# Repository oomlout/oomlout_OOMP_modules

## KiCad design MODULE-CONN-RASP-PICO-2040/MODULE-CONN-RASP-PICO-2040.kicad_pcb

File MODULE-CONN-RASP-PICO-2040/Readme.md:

Contents
========

* [MCRP2040 > ](#mcrp2040--)
	* [OOMP Parts](#oomp-parts)
	* [Images](#images)
	* [Tags](#tags)
  
![][im]
# MCRP2040 > 

- ID: MODULE-CONN-RASP-PICO-2040
- Hex ID: MCRP2040
- Name: 
- Description: 
- Long Link: [http://oom.lt/MODULE-CONN-RASP-PICO-2040](http://oom.lt/MODULE-CONN-RASP-PICO-2040)
- Short Link: [http://oom.lt/MCRP2040](http://oom.lt/MCRP2040)

## OOMP Parts

|OOMP ID|Name|Identifier|
| :---: | :---: | :---: |
|[HEAD-I01-X-PI20-01](https://github.com/oomlout/oomlout_OOMP_parts/tree/main/HEAD-I01-X-PI20-01/)|[2.54 mm 20 Pin Header](https://github.com/oomlout/oomlout_OOMP_parts/tree/main/HEAD-I01-X-PI20-01/)|[J1, J2](https://github.com/oomlout/oomlout_OOMP_parts/tree/main/HEAD-I01-X-PI20-01/)|

## Images

|kicadPcb3d|kicadPcb3dFront|kicadPcb3dBack|kicadSchem|pcbdraw|pcbdrawback|
| :---: | :---: | :---: | :---: | :---: | :---: |
|||||||

## Tags

- oompType: MODULE
- oompSize: CONN
- oompColor: RASP
- oompDesc: PICO
- oompIndex: 2040
- matchingBlock: BLOCK-CONN-RASP-PICO-2040
- oompParts: J1,HEAD-I01-X-PI20-01
- oompParts: J2,HEAD-I01-X-PI20-01
- hexID: MCRP2040
- oompID: MODULE-CONN-RASP-PICO-2040

[im]: kicadPcb3d_450.png

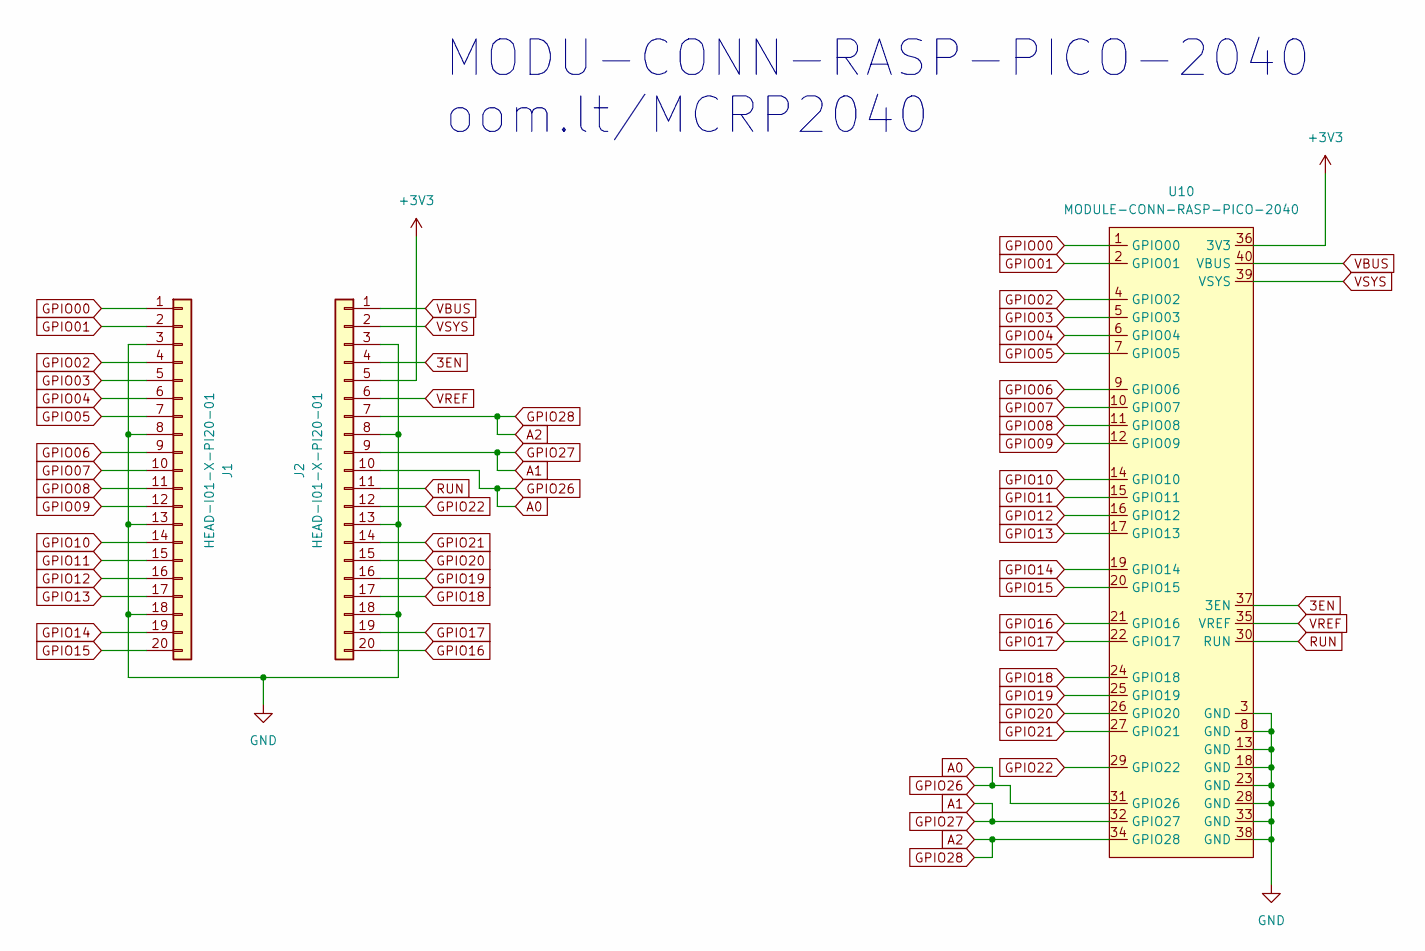
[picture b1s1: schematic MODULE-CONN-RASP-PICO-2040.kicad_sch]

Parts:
J1, J2: HEAD-I01-X-PI20-01; PinHeader_1x20_P2.54mm_Vertical
U10: MODULE-CONN-RASP-PICO-2040

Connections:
3EN: J2.4, U10.37 (3EN)
+3V3: J2.5, U10.36 (3V3)
GND: J1.3, J1.8, J1.13, J1.18, J2.3, J2.8, J2.13, J2.18, U10.3 (GND), U10.8 (GND), U10.13 (GND), U10.18 (GND), U10.23 (GND), U10.28 (GND), U10.33 (GND), U10.38 (GND)
GPIO00: J1.1, U10.1 (GPIO00)
GPIO01: J1.2, U10.2 (GPIO01)
GPIO02: J1.4, U10.4 (GPIO02)
GPIO03: J1.5, U10.5 (GPIO03)
GPIO04: J1.6, U10.6 (GPIO04)
GPIO05: J1.7, U10.7 (GPIO05)
GPIO06: J1.9, U10.9 (GPIO06)
GPIO07: J1.10, U10.10 (GPIO07)
GPIO08: J1.11, U10.11 (GPIO08)
GPIO09: J1.12, U10.12 (GPIO09)
GPIO10: J1.14, U10.14 (GPIO10)
GPIO11: J1.15, U10.15 (GPIO11)
GPIO12: J1.16, U10.16 (GPIO12)
GPIO13: J1.17, U10.17 (GPIO13)
GPIO14: J1.19, U10.19 (GPIO14)
GPIO15: J1.20, U10.20 (GPIO15)
GPIO16: J2.20, U10.21 (GPIO16)
GPIO17: J2.19, U10.22 (GPIO17)
GPIO18: J2.17, U10.24 (GPIO18)
GPIO19: J2.16, U10.25 (GPIO19)
GPIO20: J2.15, U10.26 (GPIO20)
GPIO21: J2.14, U10.27 (GPIO21)
GPIO22: J2.12, U10.29 (GPIO22)
GPIO26: J2.10, U10.31 (GPIO26)
GPIO27: J2.9, U10.32 (GPIO27)
GPIO28: J2.7, U10.34 (GPIO28)
RUN: J2.11, U10.30 (RUN)
VBUS: J2.1, U10.40 (VBUS)
VREF: J2.6, U10.35 (VREF)
VSYS: J2.2, U10.39 (VSYS)

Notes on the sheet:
MODU-CONN-RASP-PICO-2040 oom.lt/MCRP2040

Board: 2 copper layers, 4 parts (0 on the bottom side), 33 nets, no tracks yet.

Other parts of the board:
Ref**: Val**; silkscreen

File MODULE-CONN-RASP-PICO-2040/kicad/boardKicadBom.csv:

"Id";"Designator";"Package";"Quantity";"Designation";"Supplier and ref";
1;"U10";"MODULE-CONN-RASP-PICO-2040";1;"MODULE-CONN-RASP-PICO-2040";;;
2;"J1,J2";"PinHeader_1x20_P2.54mm_Vertical";2;"HEAD-I01-X-PI20-01";;;
3;"Ref**";"silkscreen";1;"Val**";;;

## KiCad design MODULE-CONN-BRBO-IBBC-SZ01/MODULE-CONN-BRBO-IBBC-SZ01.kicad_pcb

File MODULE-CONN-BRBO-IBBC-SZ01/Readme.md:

Contents
========

* [MCBI1 > ](#mcbi1--)
	* [OOMP Parts](#oomp-parts)
	* [Images](#images)
	* [Tags](#tags)
  
![][im]
# MCBI1 > 

- ID: MODULE-CONN-BRBO-IBBC-SZ01
- Hex ID: MCBI1
- Name: 
- Description: 
- Long Link: [http://oom.lt/MODULE-CONN-BRBO-IBBC-SZ01](http://oom.lt/MODULE-CONN-BRBO-IBBC-SZ01)
- Short Link: [http://oom.lt/MCBI1](http://oom.lt/MCBI1)

## OOMP Parts

|OOMP ID|Name|Identifier|
| :---: | :---: | :---: |
|[HEAD-I01-X-PI06-01](https://github.com/oomlout/oomlout_OOMP_parts/tree/main/HEAD-I01-X-PI06-01/)|[2.54 mm 6 Pin Header](https://github.com/oomlout/oomlout_OOMP_parts/tree/main/HEAD-I01-X-PI06-01/)|[J1, J2](https://github.com/oomlout/oomlout_OOMP_parts/tree/main/HEAD-I01-X-PI06-01/)|

## Images

|kicadPcb3d|kicadPcb3dFront|kicadPcb3dBack|kicadSchem|pcbdraw|pcbdrawback|
| :---: | :---: | :---: | :---: | :---: | :---: |
|||||||

## Tags

- oompType: MODULE
- oompSize: CONN
- oompColor: BRBO
- oompDesc: IBBC
- oompIndex: SZ01
- matchingBlock: BLOCK-CONN-I2C-EXTRA-01
- oompParts: J1,HEAD-I01-X-PI06-01
- oompParts: J2,HEAD-I01-X-PI06-01
- componentModules: M1,MODULE-CONN-I2C-QWIIC-01
- componentModules: M2,MODULE-CONN-I2C-QWIIC-01
- hexID: MCBI1
- oompID: MODULE-CONN-BRBO-IBBC-SZ01

[im]: kicadPcb3d_450.png

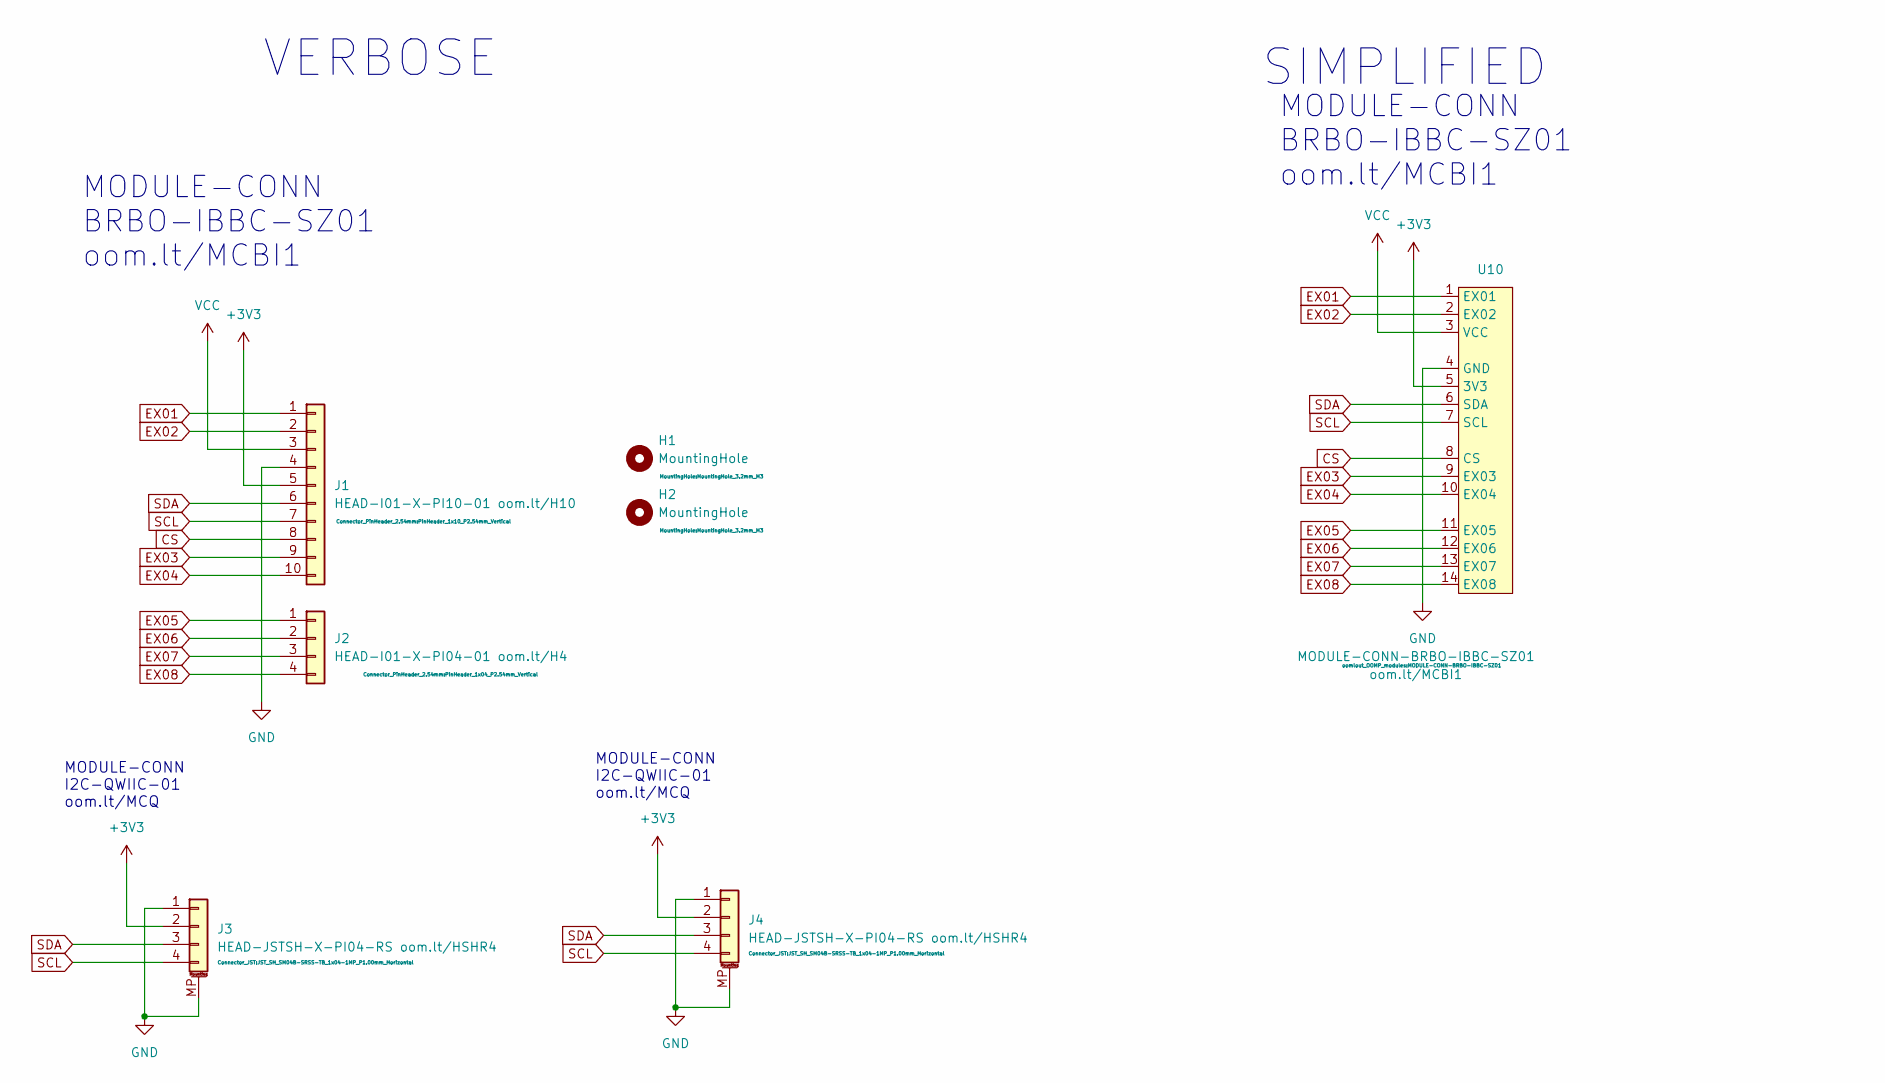
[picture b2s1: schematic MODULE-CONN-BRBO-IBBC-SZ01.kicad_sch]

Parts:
H1, H2: MountingHole; MountingHole_3.2mm_M3
J1: HEAD-I01-X-PI10-01 oom.lt/H10; PinHeader_1x10_P2.54mm_Vertical
J2: HEAD-I01-X-PI04-01 oom.lt/H4; PinHeader_1x04_P2.54mm_Vertical
J3, J4: HEAD-JSTSH-X-PI04-RS oom.lt/HSHR4; JST_SH_SM04B-SRSS-TB_1x04-1MP_P1.00mm_Horizontal
U10: MODULE-CONN-BRBO-IBBC-SZ01

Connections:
+3V3: J1.5, J3.2, J4.2
CS: J1.8, U10.8 (CS)
EX01: J1.1, U10.1 (EX01)
EX02: J1.2, U10.2 (EX02)
EX03: J1.9, U10.9 (EX03)
EX04: J1.10, U10.10 (EX04)
EX05: J2.1, U10.11 (EX05)
EX06: J2.2, U10.12 (EX06)
EX07: J2.3, U10.13 (EX07)
EX08: J2.4, U10.14 (EX08)
GND: J1.4, J3.1, J3.MP (MountPin), J4.1, J4.MP (MountPin)
SCL: J1.7, J3.4, J4.4, U10.7 (SCL)
SDA: J1.6, J3.3, J4.3, U10.6 (SDA)
VCC: J1.3

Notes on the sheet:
VERBOSE
MODULE-CONN BRBO-IBBC-SZ01 oom.lt/MCBI1
SIMPLIFIED
MODULE-CONN I2C-QWIIC-01 oom.lt/MCQ

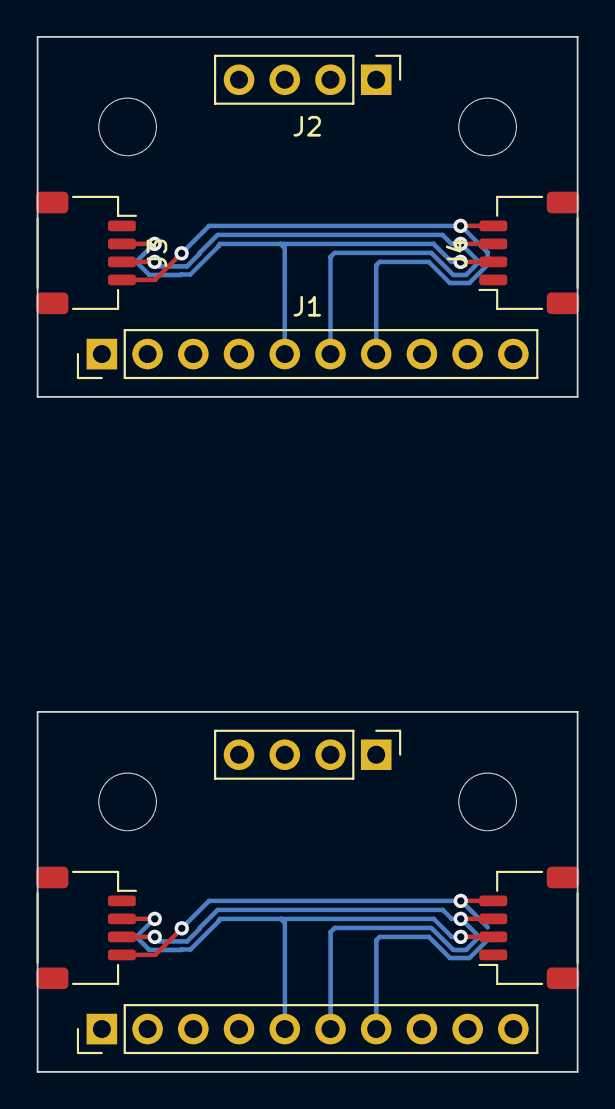
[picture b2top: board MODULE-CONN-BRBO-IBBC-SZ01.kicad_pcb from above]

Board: 2 copper layers, 30.0 x 57.5 mm, 7 parts (0 on the bottom side), 13 nets.

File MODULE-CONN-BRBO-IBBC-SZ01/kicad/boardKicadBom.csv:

"Id";"Designator";"Package";"Quantity";"Designation";"Supplier and ref";
1;"J4,J3";"JST_SH_SM04B-SRSS-TB_1x04-1MP_P1.00mm_Horizontal";2;"HEAD-JSTSH-X-PI04-RS oom.lt/HSHR4";;;
2;"J2";"PinHeader_1x04_P2.54mm_Vertical";1;"HEAD-I01-X-PI04-01 oom.lt/H4";;;
3;"U10";"MODULE-CONN-BRBO-IBBC-SZ01";1;"MODULE-CONN-BRBO-IBBC-SZ01";;;
4;"H2,H1";"MountingHole_3.2mm_M3";2;"MountingHole";;;
5;"J1";"PinHeader_1x10_P2.54mm_Vertical";1;"HEAD-I01-X-PI10-01 oom.lt/H10";;;

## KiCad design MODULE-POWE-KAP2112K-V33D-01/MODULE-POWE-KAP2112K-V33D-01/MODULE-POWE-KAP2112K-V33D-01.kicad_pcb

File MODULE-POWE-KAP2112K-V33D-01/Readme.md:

Contents
========

* [MP21123 > 3.3v](#mp21123--33v)
	* [OOMP Parts](#oomp-parts)
	* [Images](#images)
	* [Tags](#tags)
  
![][im]
# MP21123 > 3.3v

- ID: MODULE-POWE-KAP2112K-V33D-01
- Hex ID: MP21123
- Name: 3.3v
- Description: 3.3v
- Long Link: [http://oom.lt/MODULE-POWE-KAP2112K-V33D-01](http://oom.lt/MODULE-POWE-KAP2112K-V33D-01)
- Short Link: [http://oom.lt/MP21123](http://oom.lt/MP21123)

## OOMP Parts

|OOMP ID|Name|Identifier|
| :---: | :---: | :---: |
|[SENS-LG14-X-K345-01](https://github.com/oomlout/oomlout_OOMP_parts/tree/main/SENS-LG14-X-K345-01/)|[14 Pin SMD (LGA) Digital Accelerometer (ADXL345) Sensor](https://github.com/oomlout/oomlout_OOMP_parts/tree/main/SENS-LG14-X-K345-01/)|[U1](https://github.com/oomlout/oomlout_OOMP_parts/tree/main/SENS-LG14-X-K345-01/)|

## Images

|kicadPcb3d|kicadPcb3dFront|kicadPcb3dBack|kicadSchem|
| :---: | :---: | :---: | :---: |
|||||

## Tags

- oompType: MODULE
- oompSize: POWE
- oompColor: KAP2112K
- oompDesc: V33D
- oompIndex: 01
- matchingBlock: BLOCK-SENS-ACCEL-I2C-01
- oompParts: U1,SENS-LG14-X-K345-01
- hexID: MP21123
- oompID: MODULE-POWE-KAP2112K-V33D-01

[im]: kicadPcb3d_450.png

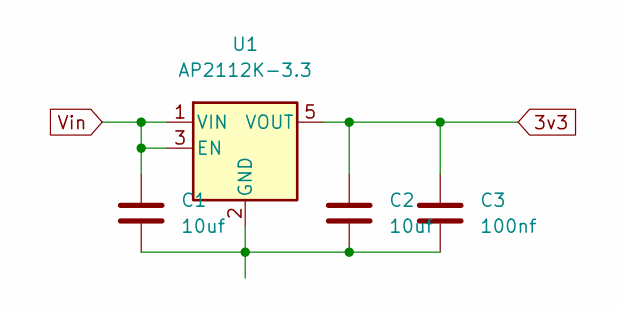
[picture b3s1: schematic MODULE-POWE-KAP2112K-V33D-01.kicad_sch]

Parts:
C1, C2: 10uf; C_0805_2012Metric
C3: 100nf; C_0603_1608Metric
U1: AP2112K-3.3; SOT-23-5

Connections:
3v3: C2.1, C3.1, U1.5 (VOUT)
unnamed: C1.2, C2.2, C3.2, U1.2 (GND)
Vin: C1.1, U1.1 (VIN), U1.3 (EN)

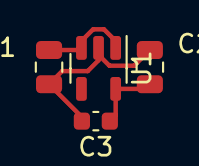
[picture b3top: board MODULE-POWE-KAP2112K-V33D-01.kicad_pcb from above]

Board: 2 copper layers, 4 parts (0 on the bottom side), 3 nets.

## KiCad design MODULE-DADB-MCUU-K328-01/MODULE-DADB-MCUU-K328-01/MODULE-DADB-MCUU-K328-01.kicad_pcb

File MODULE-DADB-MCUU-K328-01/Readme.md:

Contents
========

* [MD328M > AtMega328P](#md328m--atmega328p)
	* [Images](#images)
	* [Tags](#tags)
  
![][im]
# MD328M > AtMega328P

- ID: MODULE-DADB-MCUU-K328-01
- Hex ID: MD328M
- Name: AtMega328P
- Description: AtMega328P
- Long Link: [http://oom.lt/MODULE-DADB-MCUU-K328-01](http://oom.lt/MODULE-DADB-MCUU-K328-01)
- Short Link: [http://oom.lt/MD328M](http://oom.lt/MD328M)

## Images

|kicadPcb3d|kicadPcb3dFront|kicadPcb3dBack|kicadSchem|
| :---: | :---: | :---: | :---: |
|||||

## Tags

- oompType: MODULE
- oompSize: DADB
- oompColor: MCUU
- oompDesc: K328
- oompIndex: 01
- hexID: MD328M
- oompID: MODULE-DADB-MCUU-K328-01

[im]: kicadPcb3d_450.png

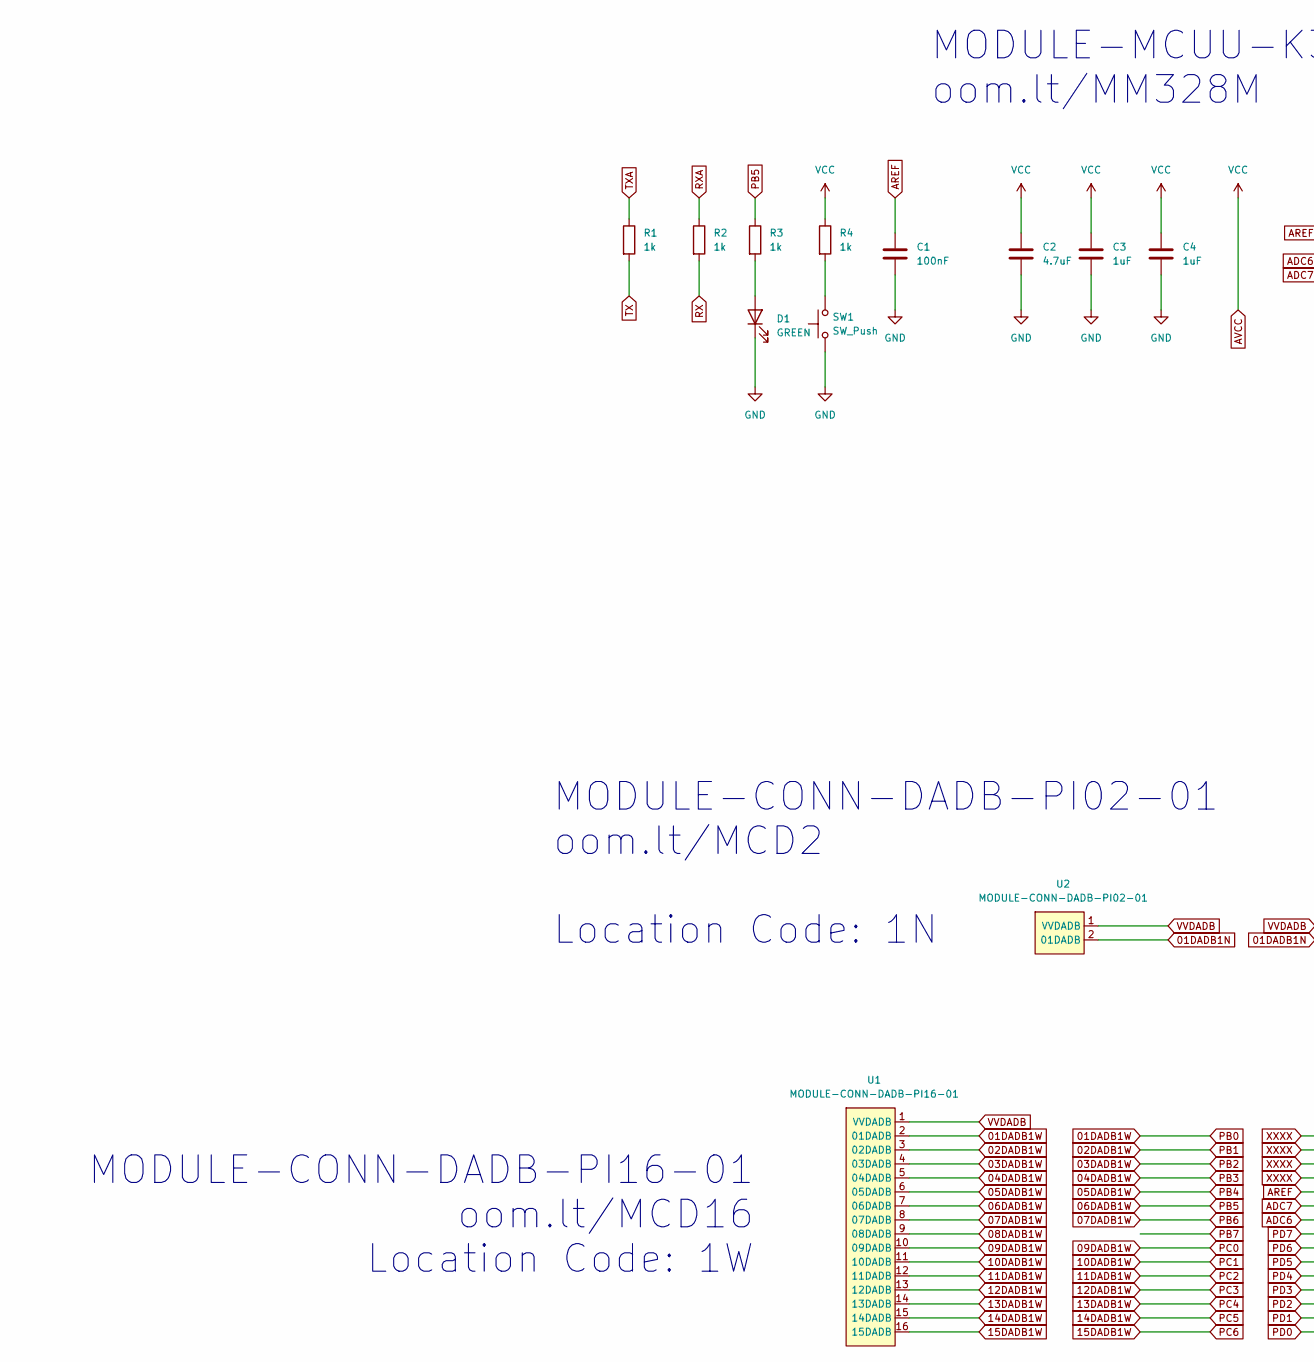
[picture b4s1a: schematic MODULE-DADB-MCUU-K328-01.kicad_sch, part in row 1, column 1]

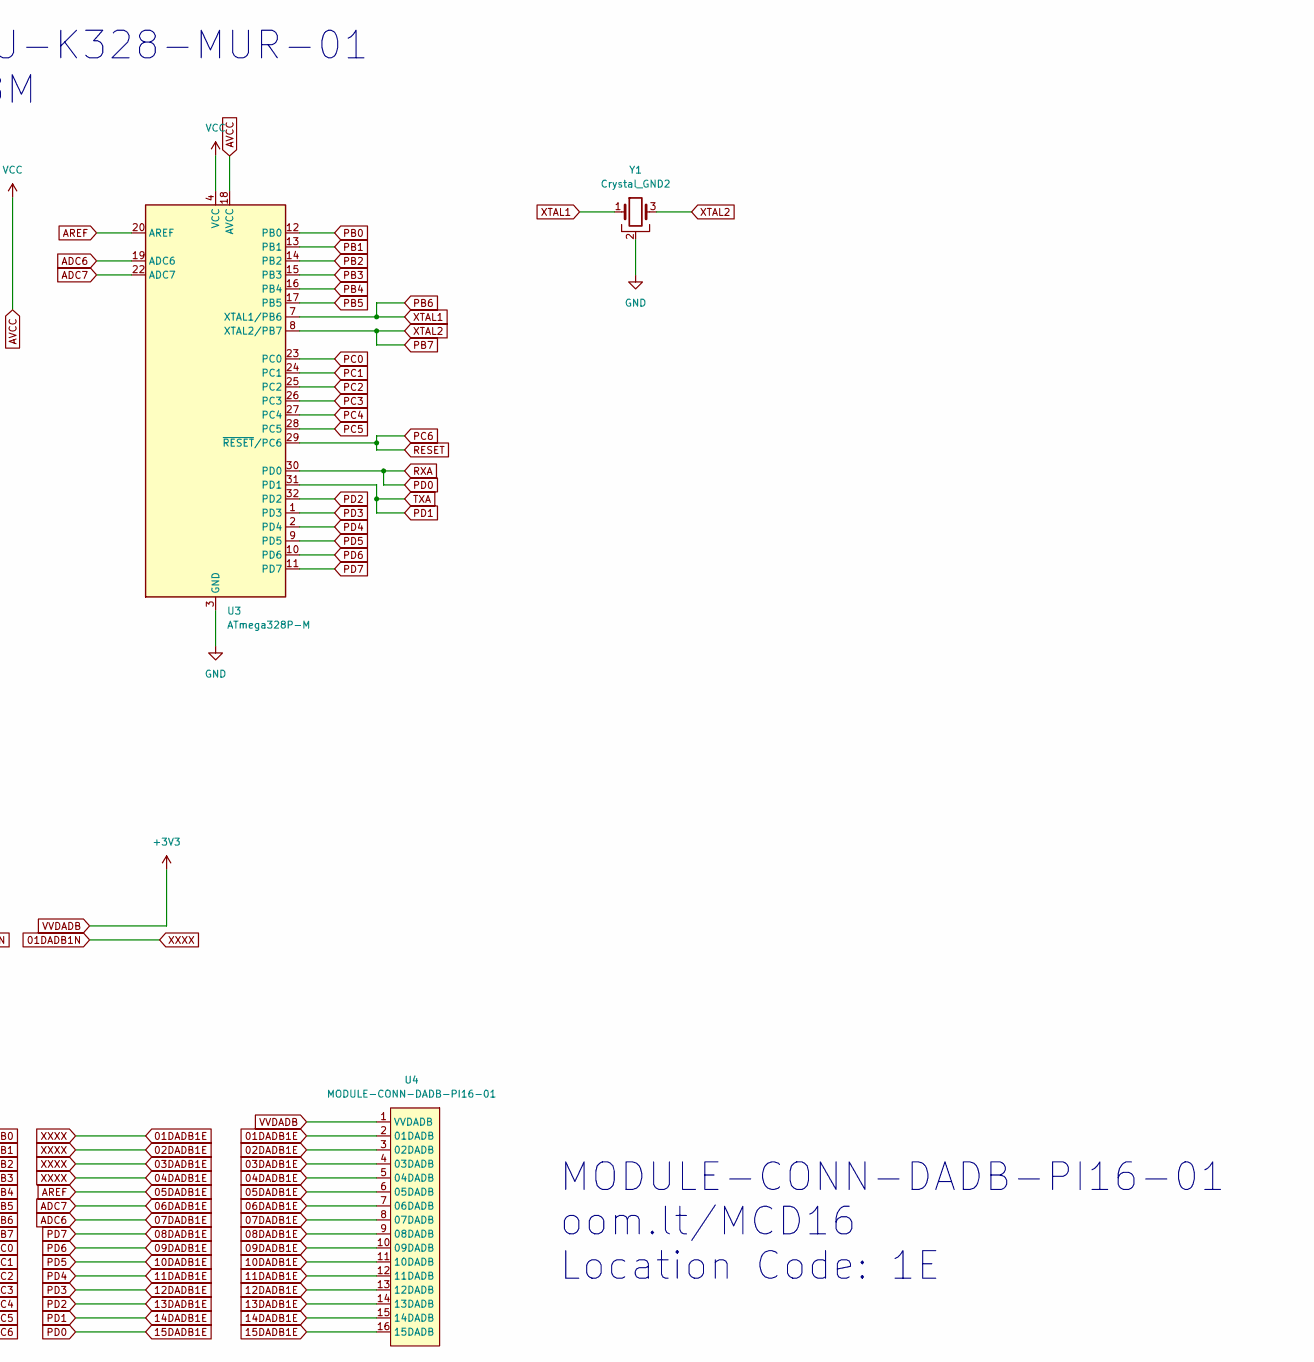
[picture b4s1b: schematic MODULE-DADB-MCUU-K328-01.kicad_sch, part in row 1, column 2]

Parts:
C1: 100nF; C_0603_1608Metric
C2: 4.7uF; C_0603_1608Metric
C3, C4: 1uF; C_0603_1608Metric
D1: GREEN; LED_0603_1608Metric
R1, R2, R3, R4: 1k; R_0603_1608Metric
SW1: SW_Push; SW_SPST_B3U-1000P
U1, U4: MODULE-CONN-DADB-PI16-01
U2: MODULE-CONN-DADB-PI02-01
U3: ATmega328P-M; QFN-32-1EP_5x5mm_P0.5mm_EP3.1x3.1mm
Y1: Crystal_GND2; PinHeader_1x03_P2.54mm_Vertical

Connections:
01DADB1E: U2.2 (01DADB), U4.2 (01DADB), U4.3 (02DADB), U4.4 (03DADB), U4.5 (04DADB)
01DADB1W: U1.2 (01DADB), U3.12 (PB0)
02DADB1W: U1.3 (02DADB), U3.13 (PB1)
03DADB1W: U1.4 (03DADB), U3.14 (PB2)
04DADB1W: U1.5 (04DADB), U3.15 (PB3)
05DADB1E: C1.1, U3.20 (AREF), U4.6 (05DADB)
05DADB1W: U1.6 (05DADB), U3.16 (PB4)
06DADB1E: U3.22 (ADC7), U4.7 (06DADB)
06DADB1W: R3.1, U1.7 (06DADB), U3.17 (PB5)
07DADB1E: U3.19 (ADC6), U4.8 (07DADB)
07DADB1W: U1.8 (07DADB), U3.7 (XTAL1/PB6), Y1.1
08DADB1E: U3.11 (PD7), U4.9 (08DADB)
08DADB1W: U1.9 (08DADB)
09DADB1E: U3.10 (PD6), U4.10 (09DADB)
09DADB1W: U1.10 (09DADB), U3.23 (PC0)
10DADB1E: U3.9 (PD5), U4.11 (10DADB)
10DADB1W: U1.11 (10DADB), U3.24 (PC1)
11DADB1E: U3.2 (PD4), U4.12 (11DADB)
11DADB1W: U1.12 (11DADB), U3.25 (PC2)
12DADB1E: U3.1 (PD3), U4.13 (12DADB)
12DADB1W: U1.13 (12DADB), U3.26 (PC3)
13DADB1E: U3.32 (PD2), U4.14 (13DADB)
13DADB1W: U1.14 (13DADB), U3.27 (PC4)
14DADB1E: R1.1, U3.31 (PD1), U4.15 (14DADB)
14DADB1W: U1.15 (14DADB), U3.28 (PC5)
15DADB1E: R2.1, U3.30 (PD0), U4.16 (15DADB)
15DADB1W: U1.16 (15DADB), U3.29 (~RESET/PC6)
AVCC: C2.1, C3.1, C4.1, R4.1, U3.4 (VCC), U3.6 (VCC), U3.18 (AVCC)
GND: C1.2, C2.2, C3.2, C4.2, D1.1 (K), SW1.1, U3.3 (GND), U3.5 (GND), U3.21 (GND), U3.33 (GND), Y1.2
unnamed: D1.2 (A), R3.2
unnamed: R4.2, SW1.2
PB7: U3.8 (XTAL2/PB7), Y1.3
RX: R2.2
TX: R1.2
VVDADB: U1.1 (VVDADB), U2.1 (VVDADB), U4.1 (VVDADB)

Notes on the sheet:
MODULE-CONN-DADB-PI02-01 oom.lt/MCD2 Location Code: 1N
MODULE-CONN-DADB-PI16-01 oom.lt/MCD16 Location Code: 1E
MODULE-CONN-DADB-PI16-01 oom.lt/MCD16 Location Code: 1W
MODULE-MCUU-K328-MUR-01 oom.lt/MM328M

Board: 2 copper layers, 15 parts (0 on the bottom side), 32 nets, no tracks yet.

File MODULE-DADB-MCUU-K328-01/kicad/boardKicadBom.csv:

"Id";"Designator";"Package";"Quantity";"Designation";"Supplier and ref";
1;"Y1";"PinHeader_1x03_P2.54mm_Vertical";1;"Crystal_GND2";;;
2;"C3,C4";"C_0603_1608Metric";2;"1uF";;;
3;"U3";"QFN-32-1EP_5x5mm_P0.5mm_EP3.1x3.1mm";1;"ATmega328P-M";;;
4;"U1,U4";"MODULE-CONN-DADB-PI16-01";2;"MODULE-CONN-DADB-PI16-01";;;
5;"C1";"C_0603_1608Metric";1;"100nF";;;
6;"C2";"C_0603_1608Metric";1;"4.7uF";;;
7;"R4,R2,R3,R1";"R_0603_1608Metric";4;"1k";;;
8;"D1";"LED_0603_1608Metric";1;"GREEN";;;
9;"U2";"MODULE-CONN-DADB-PI02-01";1;"MODULE-CONN-DADB-PI02-01";;;
10;"SW1";"SW_SPST_B3U-1000P";1;"SW_Push";;;

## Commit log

2022-10-10 Initial commit.
2022-10-11 Module massaging for IBBC-01
2022-10-12 Worked on footprintification.
2022-10-12 General workings.
2022-10-12 Fixed file locations and names.
2022-10-12 Generated new items.
2022-10-12 First Readme's
2022-10-12 Initial readmes.
2022-10-13 Module workings.
2022-10-13 Fixed a few folders.
2022-10-14 Readme update.
2022-10-14 Moved kicad stuff to it's own repository
2022-10-14 Generated module files.
2022-10-14 First run through
2022-10-17 Modules refresh.
2022-10-18 Light work.
2022-10-18 Added PCB blanks.
